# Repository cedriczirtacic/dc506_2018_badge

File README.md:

# dc506 2018 circular badge
Made for [DC506](https://twitter.com/Defcon506) in KiCad using Digikey Libs.

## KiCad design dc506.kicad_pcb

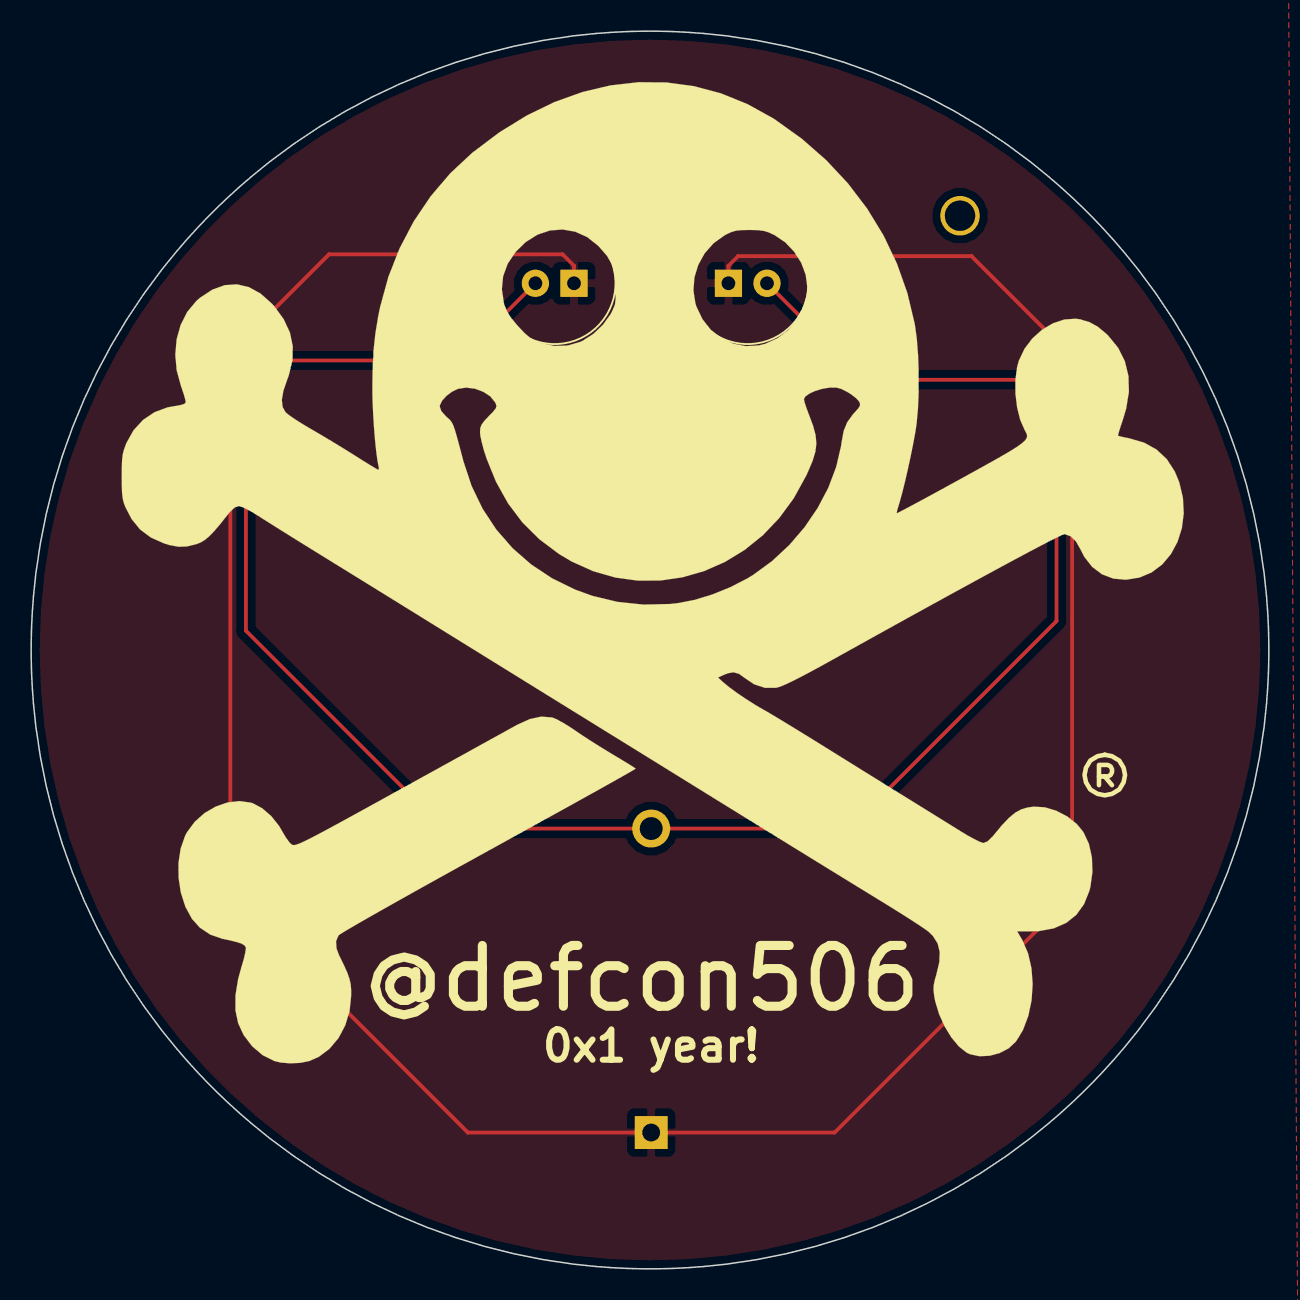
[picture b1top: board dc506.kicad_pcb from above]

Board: 2 copper layers, 81.4 x 81.4 mm, 5 parts (1 on the bottom side), 4 nets.

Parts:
BAT1: BS-7; Battery_Holder_Coin_2032_BS-7
D1, D2: LED; LED_D8.0mm
R1, R2: 1KΩ; R_Axial_DIN0204_L3.6mm_D1.6mm_P1.90mm_Vertical

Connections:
GND: BAT1.2, D1.1, D2.1
unnamed: BAT1.1, R1.2, R2.2
unnamed: D1.2, R2.1
unnamed: D2.2, R1.1
